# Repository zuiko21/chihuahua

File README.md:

# chihuahua
simple 65C02-based Single Board Computer

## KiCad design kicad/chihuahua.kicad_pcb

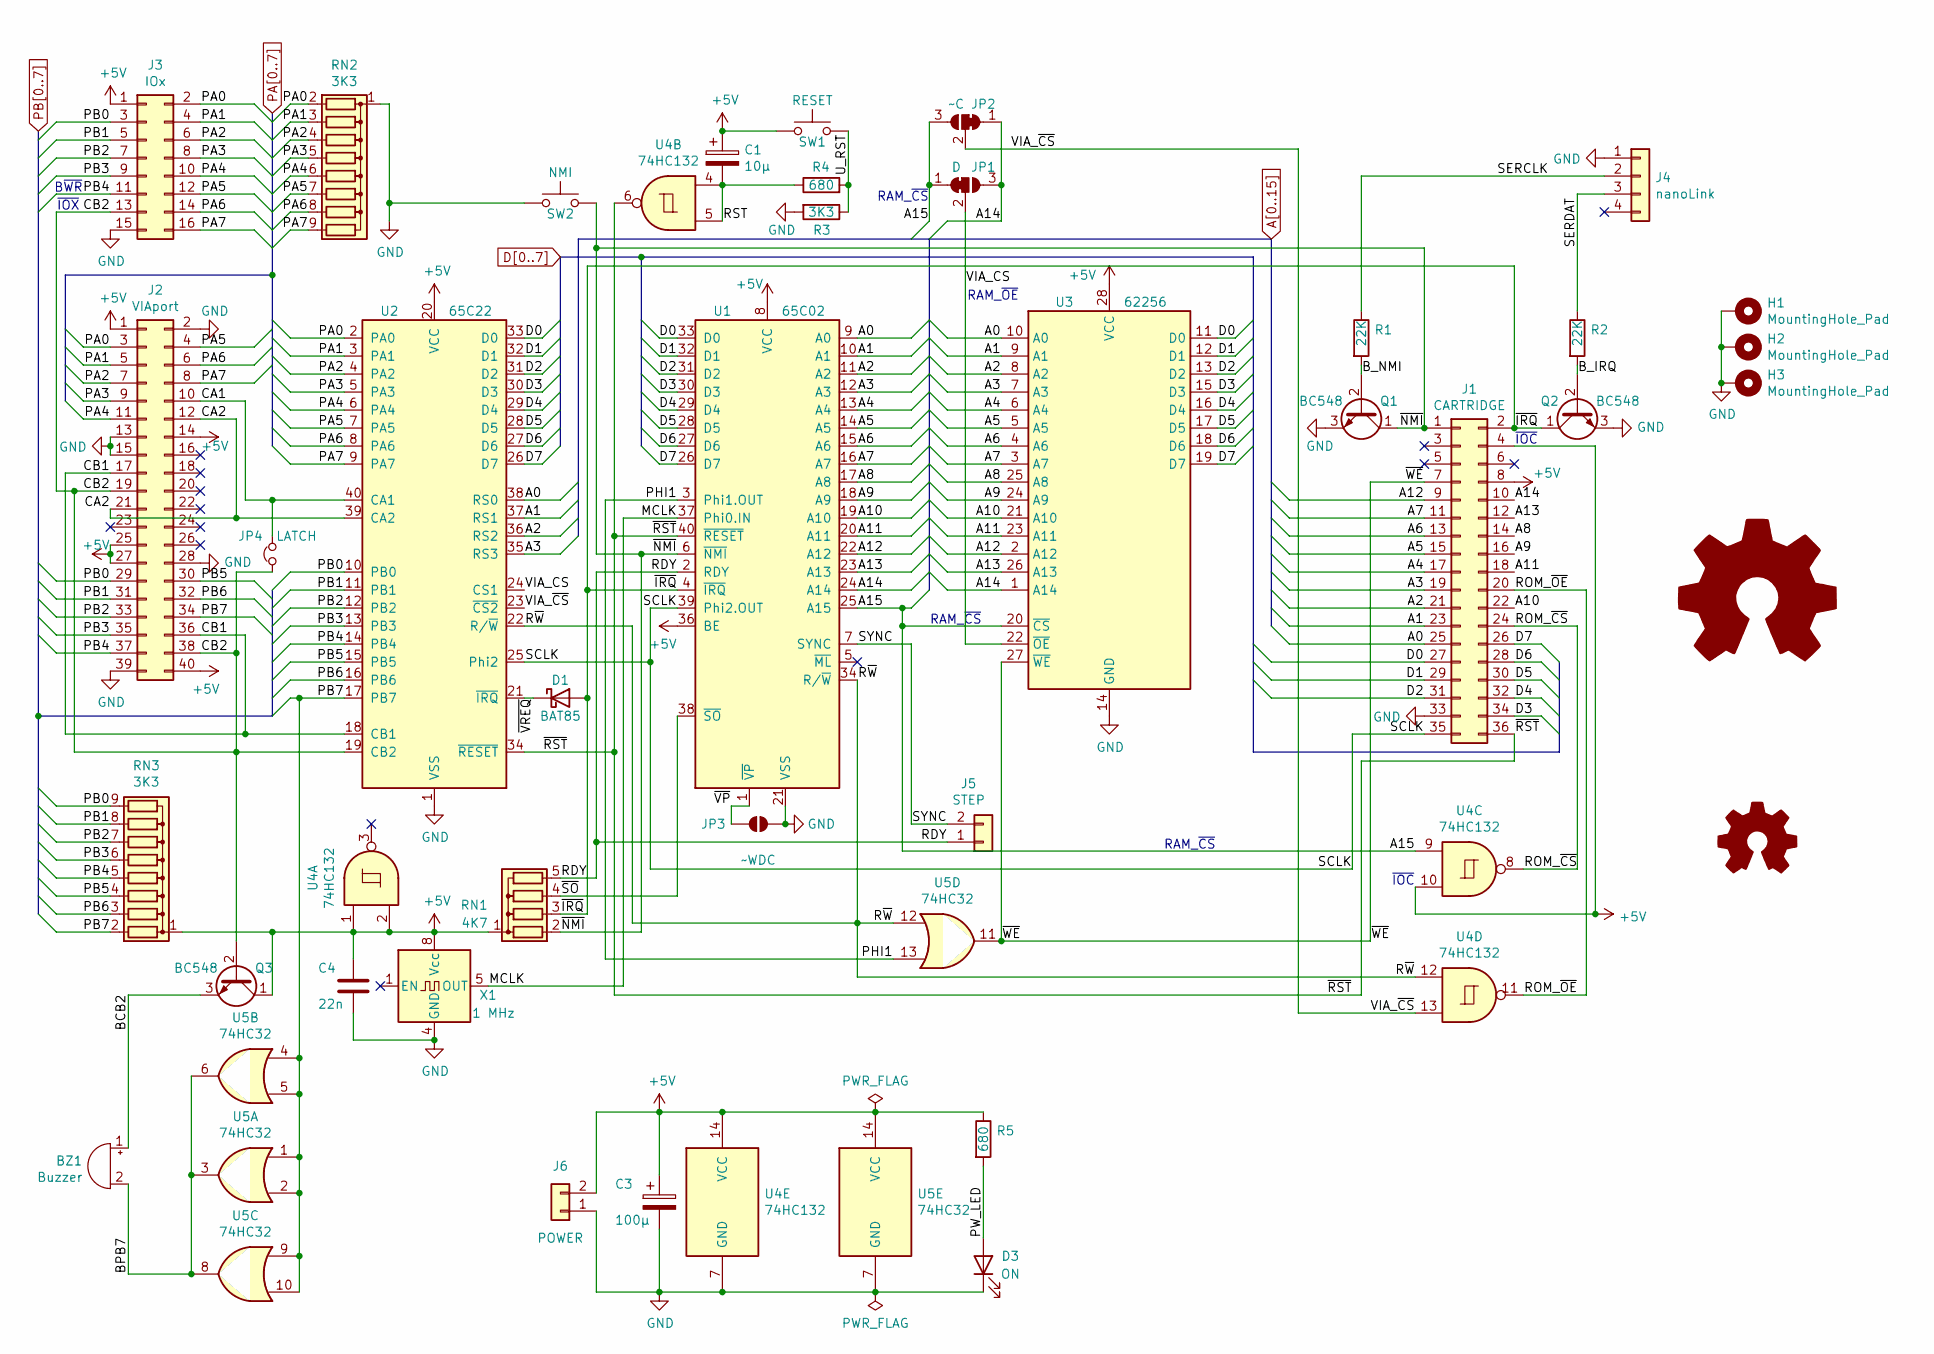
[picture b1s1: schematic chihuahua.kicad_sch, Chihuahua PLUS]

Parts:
BZ1: Buzzer; Buzzer_12x9.5RM7.6
C1: 10µ; CP_Radial_D4.0mm_P1.50mm
C3: 100µ; CP_Radial_D4.0mm_P1.50mm
C4: 22n; C_Rect_L7.2mm_W2.5mm_P5.00mm_FKS2_FKP2_MKS2_MKP2
D1: BAT85; D_DO-35_SOD27_P2.54mm_Vertical_KathodeUp
D3: ON; LED_D3.0mm
H1, H2, H3: MountingHole_Pad; MountingHole_3.2mm_M3_DIN965_Pad
J1: CARTRIDGE; PinSocket_2x18_EDGE
J2: VIAport; IDC-Header_2x20_P2.54mm_Vertical
J3: IOx; IDC-Header_2x08_P2.54mm_Vertical
J4: nanoLink; PinHeader_1x04_P2.54mm_Vertical
J5: STEP; PinHeader_1x02_P2.54mm_Vertical
J6: POWER; JST_EH_S2B-EH_1x02_P2.50mm_Horizontal
JP1: D; SolderJumper-3_P1.3mm_Bridged12_RoundedPad1.0x1.5mm
JP2: ~C; SolderJumper-3_P1.3mm_Bridged12_RoundedPad1.0x1.5mm
JP3: ~WDC; SolderJumper-2_P1.3mm_Open_RoundedPad1.0x1.5mm
JP4: LATCH; PinHeader_1x02_P2.54mm_Vertical
LOGO1: Logo_Open_Hardware_Large; OSHW-Symbol_8.9x8mm_SilkScreen
LOGO2: Logo_Open_Hardware_Small; jaqueria
Q1, Q2, Q3: BC548; TO-92_Inline
R1, R2: 22K; R_Axial_DIN0207_L6.3mm_D2.5mm_P2.54mm_Vertical
R3: 3K3; R_Axial_DIN0207_L6.3mm_D2.5mm_P2.54mm_Vertical
R4, R5: 680; R_Axial_DIN0207_L6.3mm_D2.5mm_P2.54mm_Vertical
RN1: 4K7; R_Array_SIP5
RN2, RN3: 3K3; R_Array_SIP9
SW1: RESET; SW_PUSH_6mm
SW2: NMI; SW_PUSH_6mm
U1: 65C02; DIP-40_W15.24mm_Socket
U2: 65C22; DIP-40_W15.24mm_Socket
U3: 62256; DIP-28_W15.24mm_Socket
U4: 74HC132; DIP-14_W7.62mm_Socket
U5: 74HC32; DIP-14_W7.62mm_Socket
X1: 1 MHz; Oscillator_DIP-8

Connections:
+5V: C1.1, C3.1, C4.1, J1.4, J1.8, J2.1, J2.14, J2.25, J2.27, J2.40, J3.1, J6.2, Q3.1 (C), R5.1, RN1.1 (common), RN3.1 (common), SW1.2, U1.8 (VCC), U1.36 (BE), U2.20 (VCC), U3.28 (VCC), U4.1, U4.2, U4.10, U4.14 (VCC), U5.14 (VCC), X1.8 (Vcc)
/BCB2: BZ1.1 (-), Q3.3 (E)
/BPB7: BZ1.2 (+), U5.3, U5.6, U5.8
/B_IRQ: Q2.2 (B), R2.2
/B_NMI: Q1.2 (B), R1.2
/CA1: J2.10, JP4.1, U2.40 (CA1)
/CA2: J2.12, J2.21, U2.39 (CA2)
/CB1: J2.17, J2.36, U2.18 (CB1)
/CB2: J2.19, J2.38, J3.13, JP4.2, Q3.2 (B), U2.19 (CB2)
/MCLK: U1.37 (Phi0.IN), X1.5 (OUT)
/PHI1: U1.3 (Phi1.OUT), U5.13
/PW_LED: D3.2 (A), R5.2
/RDY: J5.1, RN1.5 (R4), U1.2 (RDY)
/ROM_~CS: J1.24, U4.8
/ROM_~OE: J1.20, U4.11
/RST: C1.2, R4.1, U4.4, U4.5
/R~W: U1.34 (R/~W), U2.22 (R/~W), U4.12, U5.12
/SCLK: J1.35, U1.39 (Phi2.OUT), U2.25 (Phi2)
/SERCLK: J4.2, R1.1
/SERDAT: J4.3, R2.1
/SYNC: J5.2, U1.7 (SYNC)
/U_RST: R3.1, R4.2, SW1.1
/VIA_CS: JP1.2 (C), U2.24 (CS1), U3.22 (~OE)
/VIA_~CS: JP2.2 (C), U2.23 (~CS2), U4.13
/~IRQ: D1.2 (A), J1.2, Q2.1 (C), RN1.3 (R2), U1.4 (~IRQ)
/~NMI: J1.1, Q1.1 (C), RN1.2 (R1), SW2.2, U1.6 (~NMI)
/~RST: J1.36, U1.40 (~RESET), U2.34 (~RESET), U4.6
/~SO: RN1.4 (R3), U1.38 (~SO)
/~VP: JP3.1 (A), U1.1 (~VP)
/~VREQ: D1.1 (K), U2.21 (~IRQ)
/~WE: J1.7, U3.27 (~WE), U5.11
A0: J1.25, U1.9 (A0), U2.38 (RS0), U3.10 (A0)
A1: J1.23, U1.10 (A1), U2.37 (RS1), U3.9 (A1)
A2: J1.21, U1.11 (A2), U2.36 (RS2), U3.8 (A2)
A3: J1.19, U1.12 (A3), U2.35 (RS3), U3.7 (A3)
A4: J1.17, U1.13 (A4), U3.6 (A4)
A5: J1.15, U1.14 (A5), U3.5 (A5)
A6: J1.13, U1.15 (A6), U3.4 (A6)
A7: J1.11, U1.16 (A7), U3.3 (A7)
A8: J1.14, U1.17 (A8), U3.25 (A8)
A9: J1.16, U1.18 (A9), U3.24 (A9)
A10: J1.22, U1.19 (A10), U3.21 (A10)
A11: J1.18, U1.20 (A11), U3.23 (A11)
A12: J1.9, U1.22 (A12), U3.2 (A12)
A13: J1.12, U1.23 (A13), U3.26 (A13)
A14: J1.10, JP1.3 (B), JP2.1 (A), U1.24 (A14), U3.1 (A14)
A15: JP1.1 (A), JP2.3 (B), U1.25 (A15), U3.20 (~CS), U4.9
D0: J1.27, U1.33 (D0), U2.33 (D0), U3.11 (D0)
D1: J1.29, U1.32 (D1), U2.32 (D1), U3.12 (D1)
D2: J1.31, U1.31 (D2), U2.31 (D2), U3.13 (D2)
D3: J1.34, U1.30 (D3), U2.30 (D3), U3.15 (D3)
D4: J1.32, U1.29 (D4), U2.29 (D4), U3.16 (D4)
D5: J1.30, U1.28 (D5), U2.28 (D5), U3.17 (D5)
D6: J1.28, U1.27 (D6), U2.27 (D6), U3.18 (D6)
D7: J1.26, U1.26 (D7), U2.26 (D7), U3.19 (D7)
GND: C3.2, C4.2, D3.1 (K), H1.1, H2.1, H3.1, J1.33, J2.2, J2.13, J2.15, J2.28, J2.39, J3.15, J4.1, J6.1, JP3.2 (B), Q1.3 (E), Q2.3 (E), R3.2, RN2.1 (common), SW2.1, U1.21 (VSS), U2.1 (VSS), U3.14 (GND), U4.7 (GND), U5.7 (GND), X1.4 (GND)
PA0: J2.3, J3.2, RN2.2 (R1), U2.2 (PA0)
PA1: J2.5, J3.4, RN2.3 (R2), U2.3 (PA1)
PA2: J2.7, J3.6, RN2.4 (R3), U2.4 (PA2)
PA3: J2.9, J3.8, RN2.5 (R4), U2.5 (PA3)
PA4: J2.11, J3.10, RN2.6 (R5), U2.6 (PA4)
PA5: J2.4, J3.12, RN2.7 (R6), U2.7 (PA5)
PA6: J2.6, J3.14, RN2.8 (R7), U2.8 (PA6)
PA7: J2.8, J3.16, RN2.9 (R8), U2.9 (PA7)
PB0: J2.29, J3.3, RN3.9 (R8), U2.10 (PB0)
PB1: J2.31, J3.5, RN3.8 (R7), U2.11 (PB1)
PB2: J2.33, J3.7, RN3.7 (R6), U2.12 (PB2)
PB3: J2.35, J3.9, RN3.6 (R5), U2.13 (PB3)
PB4: J2.37, J3.11, RN3.5 (R4), U2.14 (PB4)
PB5: J2.30, RN3.4 (R3), U2.15 (PB5)
PB6: J2.32, RN3.3 (R2), U2.16 (PB6)
PB7: J2.34, RN3.2 (R1), U2.17 (PB7), U5.1, U5.2, U5.4, U5.5, U5.9, U5.10

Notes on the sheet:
RAM_~{CS}
RAM_~{OE}
~{IOC}
B~{WR}
~{IOX}

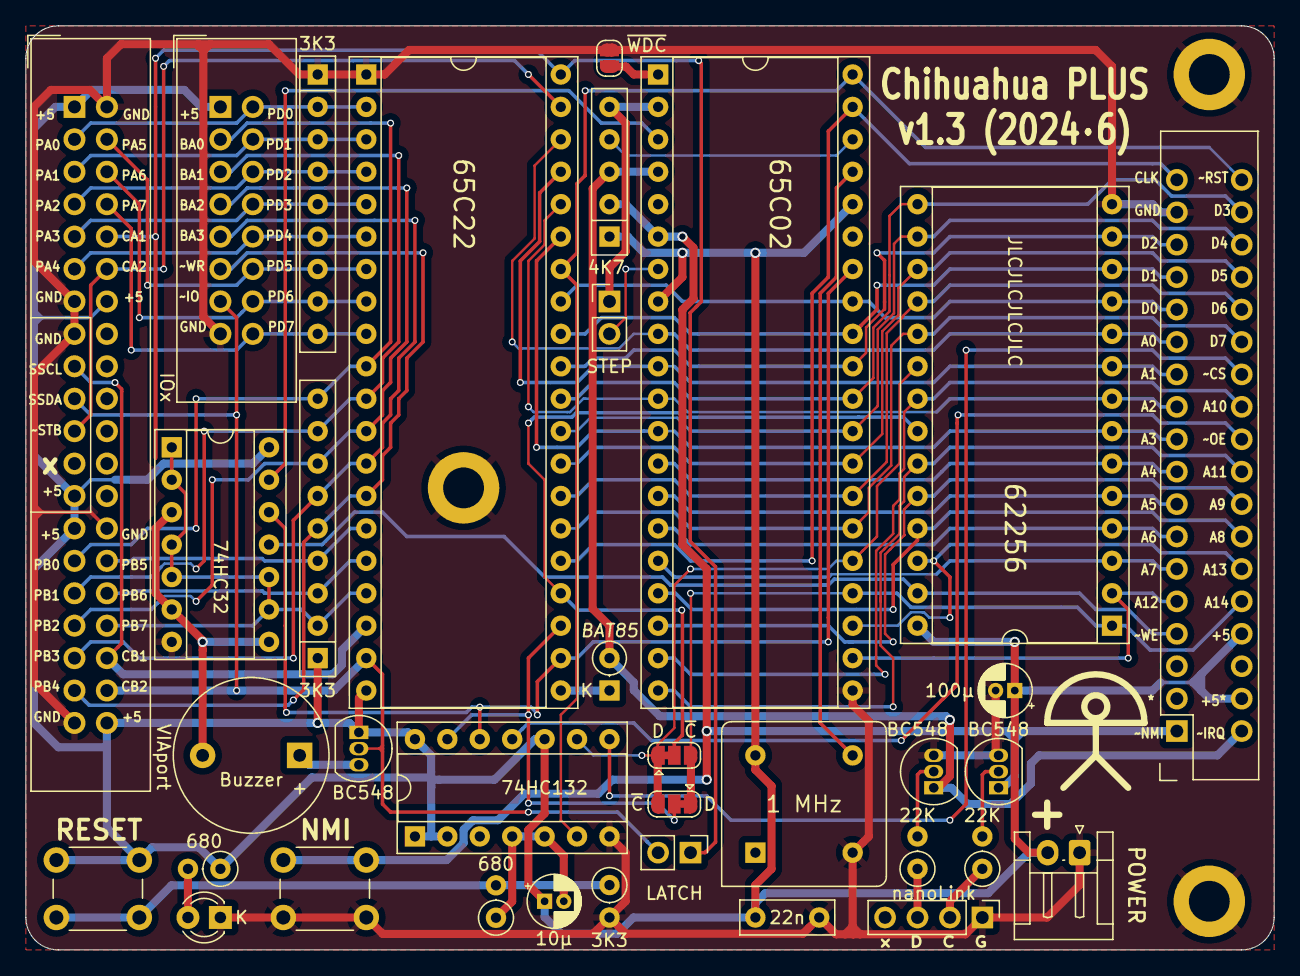
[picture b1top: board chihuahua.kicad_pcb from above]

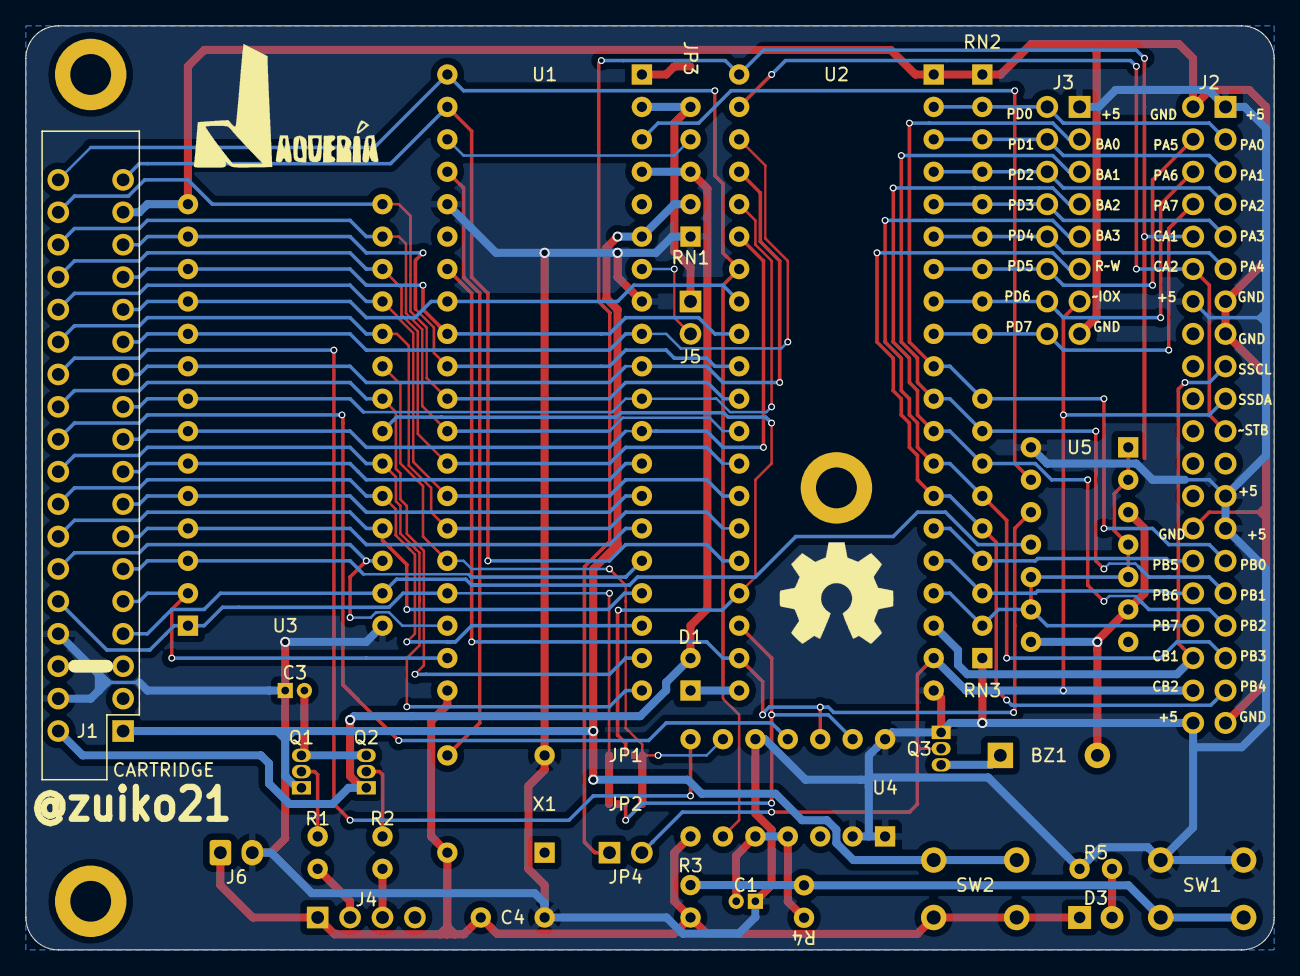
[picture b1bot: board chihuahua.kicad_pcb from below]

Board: 2 copper layers, 97.8 x 72.4 mm, 40 parts (2 on the bottom side), 72 nets.

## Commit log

2024-06-28 migrate Chihuahua to new KiCAD 8.x repository
2024-06-28 v1.3
2024-06-28 improve power planes
2024-07-25 PCB update

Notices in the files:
kicad/chihuahua.kicad_sch:
(c) 2012-2024 Carlos J. Santisteban
